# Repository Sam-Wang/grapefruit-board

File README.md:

uMeshFw Grapefruit board / debug platform
==============================================

During the last two years of sparse uMeshFw development I noticed that often a problem or a feature
cannot be properly simulated and tested. Most of the development was done on a qNode4 platform,
which (among the others) lacks support for many required peripherals and is not very debug-friendly.
It was (and still is) meant to be used in "production".

Therefore I decided to specify a new debug board / platform which should ease the development
of the uMeshFw firmware and uMesh protocol stack features.

Also, I had a feeling that qNodeX names are a bit boring.

This repository is a Work in Progress and is still incomplete. Full project description can be
found on the [project page](http://qyx.krtko.org/projects/umeshfw-grapefruit-board/)

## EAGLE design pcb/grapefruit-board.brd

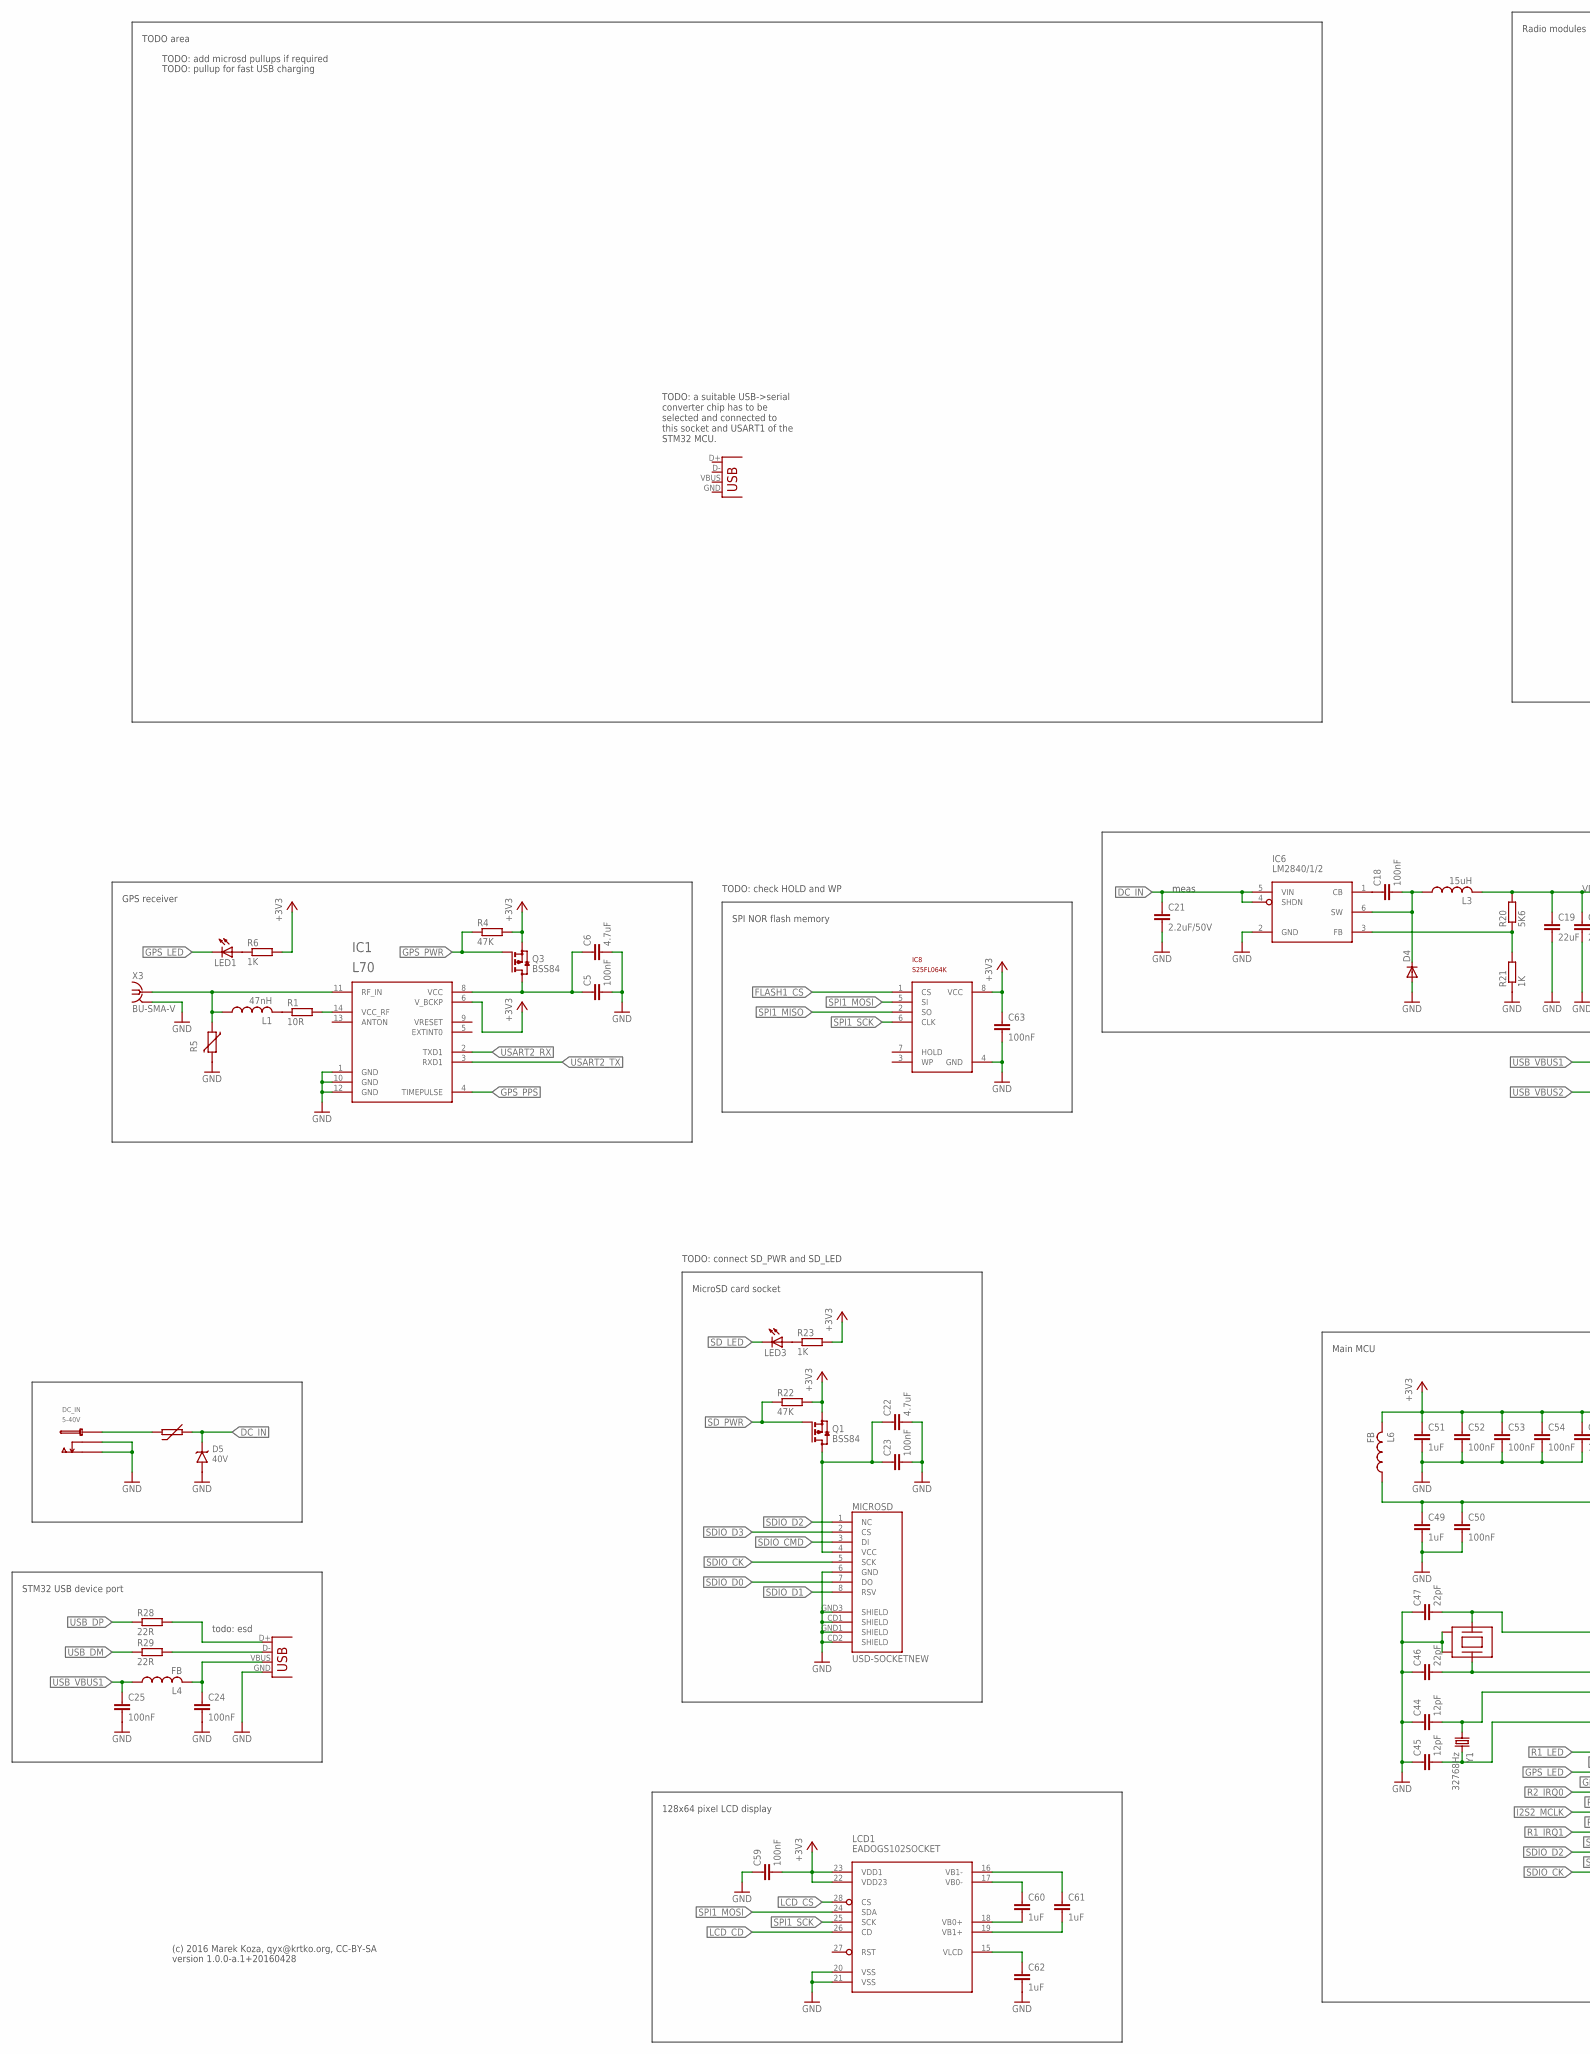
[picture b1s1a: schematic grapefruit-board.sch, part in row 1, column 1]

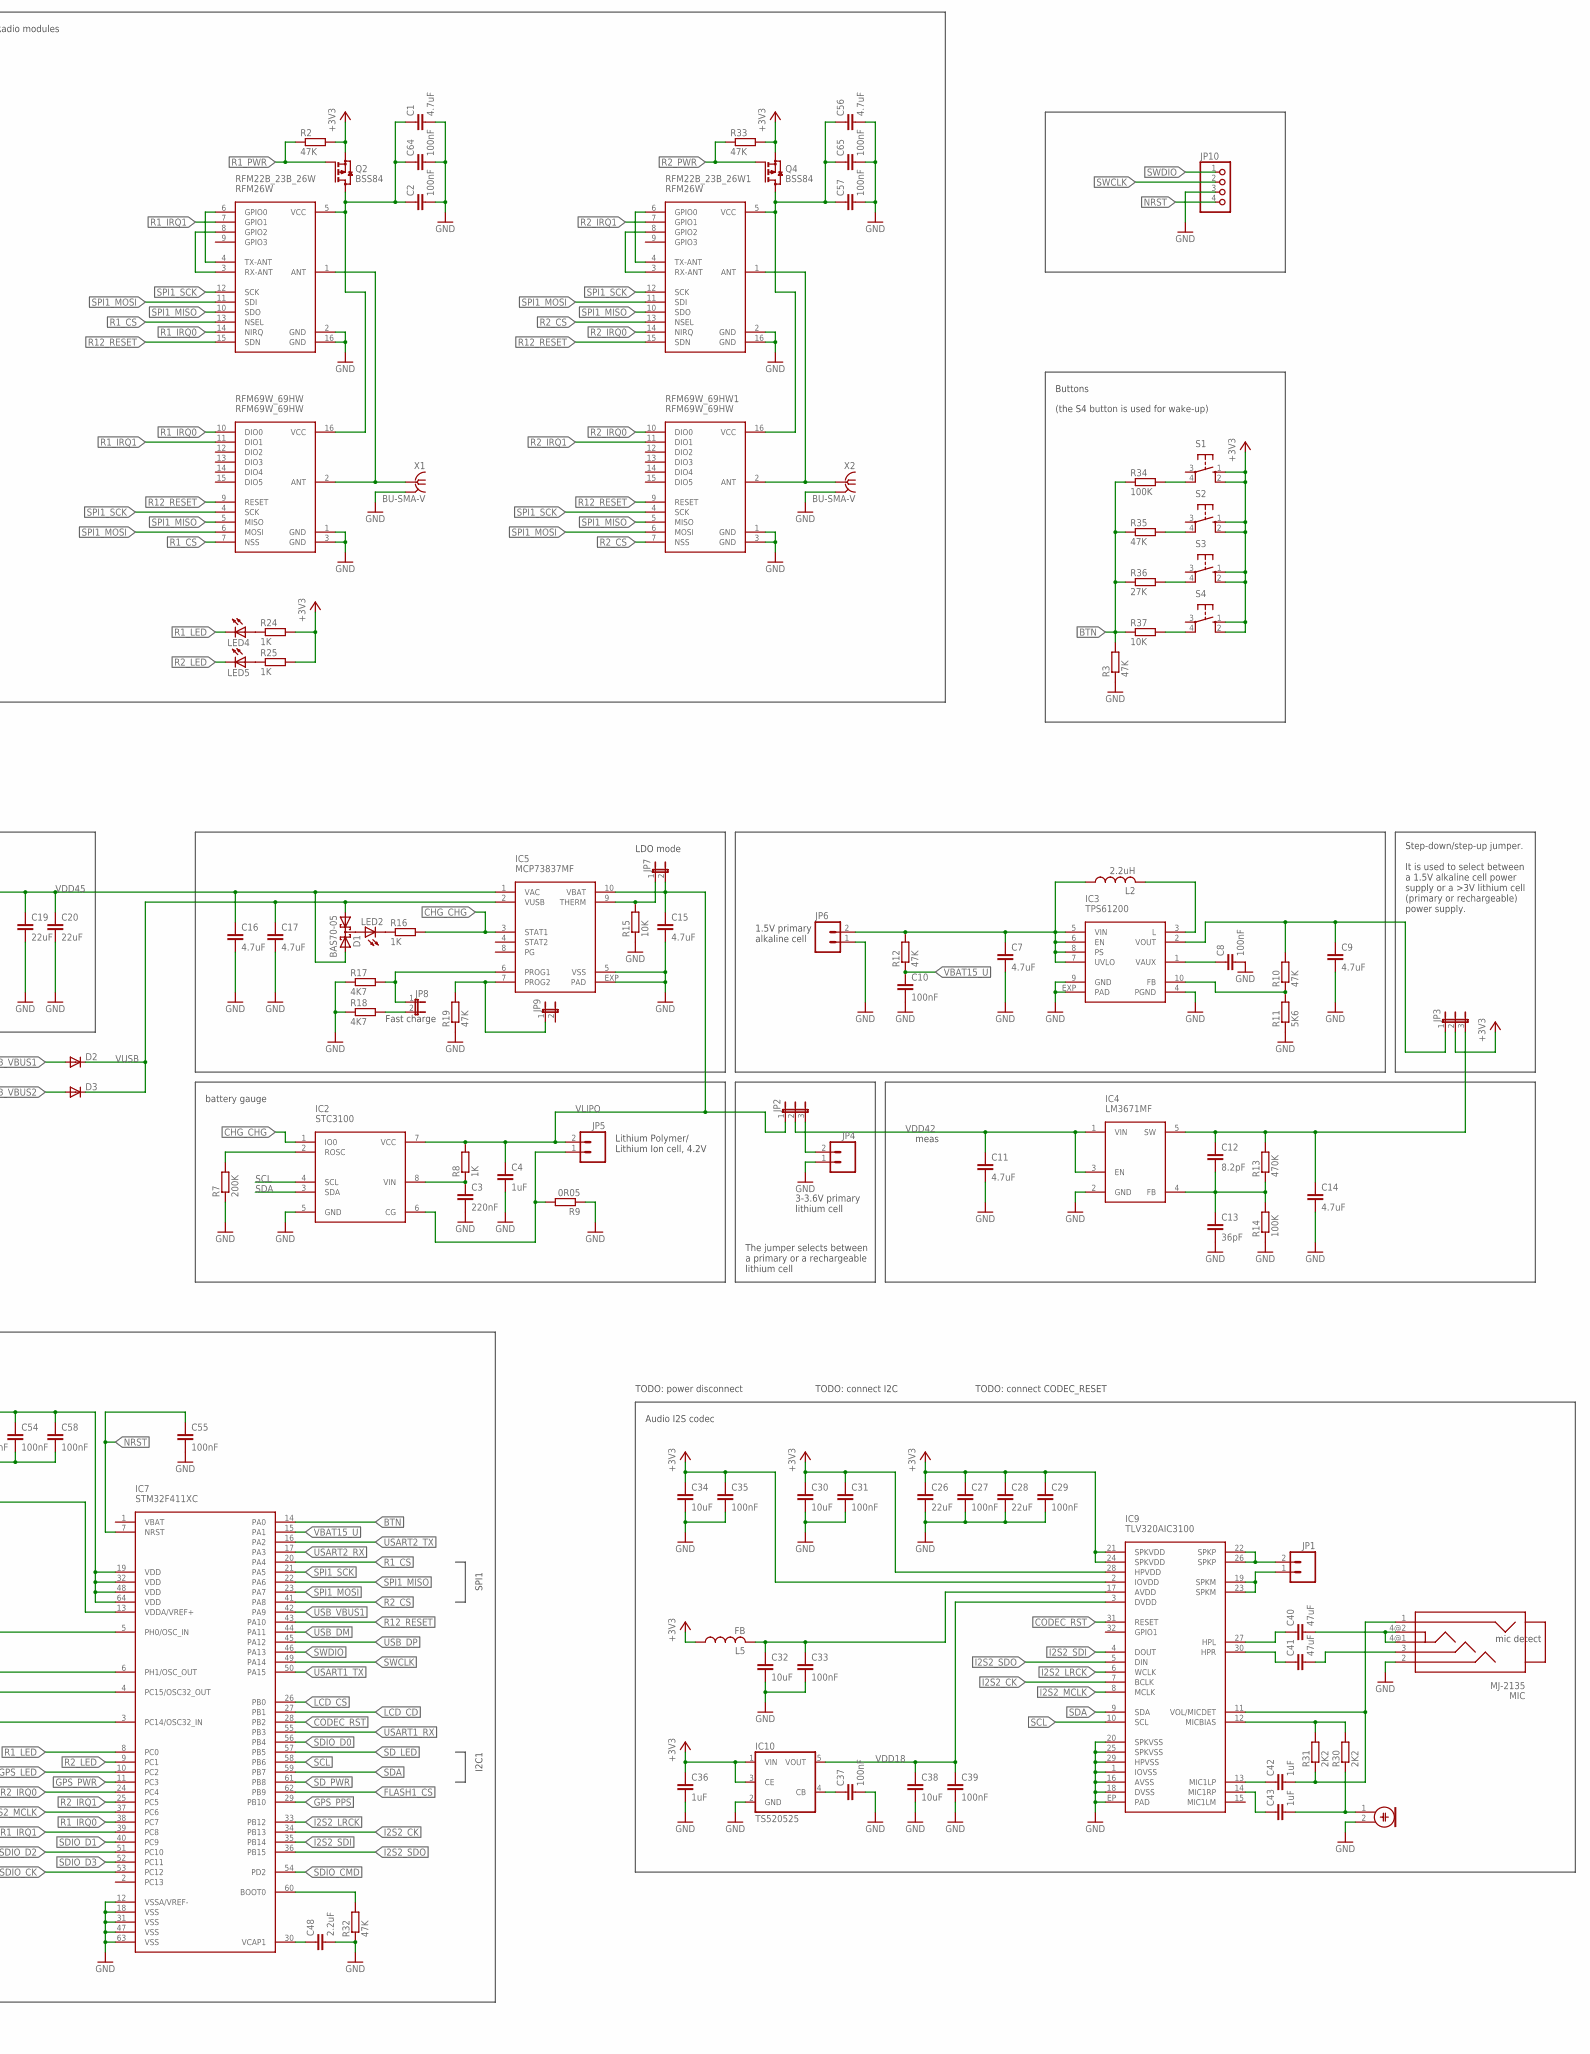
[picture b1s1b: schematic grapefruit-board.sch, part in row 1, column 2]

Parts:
C1, C6, C7, C9, C11, C14, C15, C16, C17, C22, C56: 4.7uF; C0805
C2, C5, C8, C10, C18, C23, C24, C25, C27, C29, C31, C33, C35, C37, C39, C50, C52, C53, C54, C55, C57, C58, C59, C63, C64, C65: 100nF; C0603
C3: 220nF; C0603
C4, C42, C43, C49, C51, C60, C61, C62: 1uF; C0603
C12: 8.2pF; C0603
C13: 36pF; C0603
C19, C20, C26, C28: 22uF; C1206
C21: 2.2uF/50V; C1206
C30, C32, C34, C38: 10uF; C1206
C36: 1uF; C0805
C40, C41: 47uF; C1206
C44, C45: 12pF; C0603
C46, C47: 22pF; C0603
C48: 2.2uF; C0805
D1: BAS70-05; SOT23
D2, D3, D4: DIODE-MICROMELF-W; MICROMELF-W
D5: 40V; SMA_DIODE
DC_IN: 5-40V; DC_JACK
IC1: L70
IC2: STC3100; MSOP8
IC3: TPS61200; DFN10-3X3
IC4: LM3671MF; SOT23-5
IC5: MCP73837MF; DFN10-3X3
IC6: LM2840/1/2; SOT23-6
IC7: STM32F411XC; LQFP64
IC8: S25FL064K; SO-08M
IC9: TLV320AIC3100; QFN32
IC10: TS520525; SOT25
JP1, JP4, JP5, JP6: M02JST-PTH-2; JST-2-PTH
JP2, JP3: JP2E; JP2
JP7, JP8, JP9: JP1E; JP1
JP10: PINHD-1X4; 1X04
L1: 47nH; L2012C
L2: 2.2uH; L2012C
L3: 15uH; L3225M
L4, L5, L6: FB; L2012C
LCD1: EADOGS102SOCKET; EADOGS-SOCKET
LED1, LED2, LED3, LED4, LED5: LEDCHIP-LED0603; CHIP-LED0603
M1: ELECTRET_MICROPHON-WM-62PC/62PK; WM-62PC/62PK
MIC: MJ-2135; JACK_35_4POLE
MICROSD: USD-SOCKETNEW; MICRO-SD-SOCKET-PP
Q1, Q2, Q3, Q4: BSS84; SOT23
R1: 10R; R0603
R2, R3, R4, R10, R12, R19, R22, R32, R33, R35: 47K; R0603
R5: VARISTORCN0805; CT/CN0805
R6, R8, R16, R21, R23, R24, R25: 1K; R0603
R7: 200K; R0603
R9: 0R05; R0805
R11, R20: 5K6; R0603
R13: 470K; R0603
R14, R34: 100K; R0603
R15, R37: 10K; R0603
R17, R18: 4K7; R0603
R28, R29: 22R; R0603
R30, R31: 2K2; R0603
R36: 27K; R0603
RFM22B_23B_26W, RFM22B_23B_26W1: RFM26W; MODULE_16X16_16PIN
RFM69W_69HW, RFM69W_69HW1: RFM69W_69HW; MODULE_20X12_16PIN
S1, S2, S3, S4: 10-XX; B3F-10XX
U$1: XTAL-7M; XTAL_7M
U$2: PTC_FUSE1210; PTC1210
X1, X2, X3: BU-SMA-V
X4, X5: USB-MICROB
Y1: 32768Hz; TC26H

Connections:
+3V3: C26.1, C27.1, C28.1, C29.1, C30.1, C31.1, C34.1, C35.1, C36.1, C51.1, C52.1, C53.1, C54.1, C58.1, C59.2, C63.1, IC1.6 (V_BCKP), IC7.19 (VDD), IC7.32 (VDD), IC7.48 (VDD), IC7.64 (VDD), IC8.8 (VCC), IC9.2 (IOVDD), IC9.21 (SPKVDD), IC9.24 (SPKVDD), IC9.28 (HPVDD), IC10.1 (VIN), IC10.3 (CE), JP3.2, L5.1, L6.2, LCD1.22 (VDD23), LCD1.23 (VDD1), Q1.2 (S), Q2.2 (S), Q3.2 (S), Q4.2 (S), R2.2, R4.2, R6.2, R22.2, R23.2, R24.2, R25.2, R33.2, S1.1 (S), S1.2 (S1), S2.1 (S), S2.2 (S1), S3.1 (S), S3.2 (S1), S4.1 (S), S4.2 (S1)
BTN: IC7.14 (PA0), R3.2, R34.1, R35.1, R36.1, R37.1
BTN1: R34.2, S1.4 (P1)
BTN2: R35.2, S2.4 (P1)
BTN3: R36.2, S3.4 (P1)
BTN4: R37.2, S4.4 (P1)
CHG_CHG: IC2.1 (IO0), IC5.3 (STAT1), R16.2
CODEC_RST: IC7.28 (PB2), IC9.31 (RESET)
DC_IN: C21.1, D5.K, IC6.4 (SHDN), IC6.5 (VIN), U$2.2
FLASH1_CS: IC7.62 (PB9), IC8.1 (CS)
GND: C1.2, C2.2, C3.2, C4.2, C5.2, C6.2, C7.2, C8.2, C9.2, C10.2, C11.2, C13.2, C14.2, C15.2, C16.2, C17.2, C19.2, C20.2, C21.2, C22.2, C23.2, C24.2, C25.2, C26.2, C27.2, C28.2, C29.2, C30.2, C31.2, C32.2, C33.2, C34.2, C35.2, C36.2, C37.2, C38.2, C39.2, C44.1, C45.1, C46.1, C47.1, C48.2, C49.2, C50.2, C51.2, C52.2, C53.2, C54.2, C55.2, C56.2, C57.2, C58.2, C59.1, C62.2, C63.2, C64.2, C65.2, D4.A, D5.A, DC_IN.O, DC_IN.OSW, IC1.1 (GND), IC1.10 (GND), IC1.12 (GND), IC2.5 (GND), IC3.4 (PGND), IC3.9 (GND), IC3.EXP (PAD), IC4.2 (GND), IC5.5 (VSS), IC5.EXP (PAD), IC6.2 (GND), IC7.12 (VSSA/VREF-), IC7.18 (VSS), IC7.31 (VSS), IC7.47 (VSS), IC7.63 (VSS), IC8.4 (GND), IC9.1 (IOVSS), IC9.16 (AVSS), IC9.18 (DVSS), IC9.20 (SPKVSS), IC9.25 (SPKVSS), IC9.29 (HPVSS), IC9.EP (PAD), IC10.2 (GND), JP4.1, JP6.1, JP10.3, LCD1.20 (VSS), LCD1.21 (VSS), M1.2, MIC.2, MICROSD.6 (GND), MICROSD.CD1 (SHIELD), MICROSD.CD2 (SHIELD), MICROSD.GND1 (SHIELD), MICROSD.GND3 (SHIELD), R3.1, R5.2, R7.1, R9.1, R11.1, R14.1, R15.1, R17.1, R18.1, R19.1, R21.1, R32.1, RFM22B_23B_26W.2 (GND), RFM22B_23B_26W.16 (GND), RFM22B_23B_26W1.2 (GND), RFM22B_23B_26W1.16 (GND), RFM69W_69HW.1 (GND), RFM69W_69HW.3 (GND), RFM69W_69HW1.1 (GND), RFM69W_69HW1.3 (GND), U$1.2 (G1), U$1.4 (G2), X1.2, X1.3 (2), X1.4 (2), X1.5 (2), X2.2, X2.3 (2), X2.4 (2), X2.5 (2), X3.2, X3.3 (2), X3.4 (2), X3.5 (2), X4.GND
GPS_LED: IC7.10 (PC2), LED1.C
GPS_PPS: IC1.4 (TIMEPULSE), IC7.29 (PB10)
GPS_PWR: IC7.11 (PC3), Q3.1 (G), R4.1
I2S2_CK: IC7.34 (PB13), IC9.7 (BCLK)
I2S2_LRCK: IC7.33 (PB12), IC9.6 (WCLK)
I2S2_MCLK: IC7.37 (PC6), IC9.8 (MCLK)
I2S2_SDI: IC7.35 (PB14), IC9.4 (DOUT)
I2S2_SDO: IC7.36 (PB15), IC9.5 (DIN)
LCD_CD: IC7.27 (PB1), LCD1.26 (CD)
LCD_CS: IC7.26 (PB0), LCD1.28 (CS)
unnamed: RFM22B_23B_26W1.1 (ANT), RFM69W_69HW1.2 (ANT), X2.1
unnamed: RFM22B_23B_26W.1 (ANT), RFM69W_69HW.2 (ANT), X1.1
unnamed: L1.2, R1.1
unnamed: IC1.11 (RF_IN), L1.1, R5.1, X3.1
unnamed: IC1.14 (VCC_RF), R1.2
unnamed: C1.1, C2.1, C64.1, Q2.3 (D), RFM22B_23B_26W.5 (VCC), RFM69W_69HW.16 (VCC)
unnamed: LED1.A, R6.1
unnamed: C5.1, C6.1, IC1.8 (VCC), Q3.3 (D)
unnamed: C7.1, IC3.5 (VIN), IC3.6 (EN), IC3.7 (UVLO), IC3.8 (PS), JP6.2, L2.1, R12.2
unnamed: JP2.3, JP4.2
unnamed: IC2.6 (CG), JP5.1, R9.2
unnamed: IC5.9 (THERM), JP7.1, R15.2
unnamed: IC5.6 (PROG1), JP8.1, R17.2
unnamed: C12.1, C14.1, IC4.5 (SW), JP3.3, R13.2
unnamed: C3.1, IC2.8 (VIN), R8.1
unnamed: C8.1, IC3.1 (VAUX)
unnamed: IC2.2 (ROSC), R7.2
unnamed: C9.1, IC3.2 (VOUT), JP3.1, R10.2
unnamed: IC3.3 (L), L2.2
unnamed: C12.2, C13.1, IC4.4 (FB), R13.1, R14.2
unnamed: IC3.10 (FB), R10.1, R11.2
unnamed: JP8.2, R18.2
unnamed: LED2.C, R16.1
unnamed: D1.3 (C), LED2.A
unnamed: IC5.7 (PROG2), JP9.1, R19.2
unnamed: C18.1, IC6.1 (CB)
unnamed: C18.2, D4.C, IC6.6 (SW), L3.1
unnamed: IC6.3 (FB), R20.1, R21.2
unnamed: C22.1, C23.1, MICROSD.4 (VCC), Q1.3 (D)
unnamed: LED3.A, R23.1
unnamed: LED4.A, R24.1
unnamed: LED5.A, R25.1
unnamed: R28.2, X4.D+
unnamed: R29.2, X4.D-
unnamed: C24.1, L4.2, X4.VBUS
unnamed: C43.1, IC9.14 (MIC1RP)
unnamed: C32.1, C33.1, IC9.17 (AVDD), L5.2
unnamed: C37.1, IC10.4 (CB)
unnamed: C40.2, MIC.4@1 (4), MIC.4@2 (4)
unnamed: C41.2, MIC.3
unnamed: C41.1, IC9.30 (HPR)
unnamed: C40.1, IC9.27 (HPL)
unnamed: C44.2, IC7.4 (PC15/OSC32_OUT), Y1.1
unnamed: C42.1, IC9.13 (MIC1LP)
unnamed: C42.2, IC9.11 (VOL/MICDET), MIC.1, R31.1
unnamed: C43.2, M1.1, R30.1
unnamed: IC9.12 (MICBIAS), R30.2, R31.2
unnamed: IC9.22 (SPKP), IC9.26 (SPKP), JP1.2
unnamed: IC9.19 (SPKM), IC9.23 (SPKM), JP1.1
unnamed: C45.2, IC7.3 (PC14/OSC32_IN), Y1.2
unnamed: DC_IN.C, U$2.1
unnamed: C47.2, IC7.5 (PH0/OSC_IN), U$1.1
unnamed: C46.2, IC7.6 (PH1/OSC_OUT), U$1.3 (2)
unnamed: C56.1, C57.1, C65.1, Q4.3 (D), RFM22B_23B_26W1.5 (VCC), RFM69W_69HW1.16 (VCC)
unnamed: IC7.60 (BOOT0), R32.2
unnamed: C48.1, IC7.30 (VCAP1)
unnamed: C49.1, C50.1, IC7.13 (VDDA/VREF+), L6.1
unnamed: C60.1, LCD1.17 (VB0-)
unnamed: C61.1, LCD1.16 (VB1-)
unnamed: C60.2, LCD1.18 (VB0+)
unnamed: C61.2, LCD1.19 (VB1+)
unnamed: C62.1, LCD1.15 (VLCD)
NRST: C55.1, IC7.7 (NRST), JP10.4
R1_CS: IC7.20 (PA4), RFM22B_23B_26W.13 (NSEL), RFM69W_69HW.7 (NSS)
R1_DIO0: RFM22B_23B_26W.4 (TX-ANT), RFM22B_23B_26W.6 (GPIO0)
R1_DIO2: RFM22B_23B_26W.3 (RX-ANT), RFM22B_23B_26W.8 (GPIO2)
R1_IRQ0: IC7.38 (PC7), RFM22B_23B_26W.14 (NIRQ), RFM69W_69HW.10 (DIO0)
R1_IRQ1: IC7.39 (PC8), RFM22B_23B_26W.7 (GPIO1), RFM69W_69HW.11 (DIO1)
R1_LED: IC7.8 (PC0), LED4.C
R1_PWR: Q2.1 (G), R2.1
R2_CS: IC7.41 (PA8), RFM22B_23B_26W1.13 (NSEL), RFM69W_69HW1.7 (NSS)
R2_DIO0: RFM22B_23B_26W1.4 (TX-ANT), RFM22B_23B_26W1.6 (GPIO0)
R2_DIO2: RFM22B_23B_26W1.3 (RX-ANT), RFM22B_23B_26W1.8 (GPIO2)
R2_IRQ0: IC7.24 (PC4), RFM22B_23B_26W1.14 (NIRQ), RFM69W_69HW1.10 (DIO0)
R2_IRQ1: IC7.25 (PC5), RFM22B_23B_26W1.7 (GPIO1), RFM69W_69HW1.11 (DIO1)
R2_LED: IC7.9 (PC1), LED5.C
R2_PWR: Q4.1 (G), R33.1
R12_RESET: IC7.43 (PA10), RFM22B_23B_26W.15 (SDN), RFM22B_23B_26W1.15 (SDN), RFM69W_69HW.9 (RESET), RFM69W_69HW1.9 (RESET)
SCL: IC2.4 (SCL), IC7.58 (PB6), IC9.10 (SCL)
SDA: IC2.3 (SDA), IC7.59 (PB7), IC9.9 (SDA)
SDIO_CK: IC7.53 (PC12), MICROSD.5 (SCK)
SDIO_CMD: IC7.54 (PD2), MICROSD.3 (DI)
SDIO_D0: IC7.56 (PB4), MICROSD.7 (DO)
SDIO_D1: IC7.40 (PC9), MICROSD.8 (RSV)
SDIO_D2: IC7.51 (PC10), MICROSD.1 (NC)
SDIO_D3: IC7.52 (PC11), MICROSD.2 (CS)
SD_LED: IC7.57 (PB5), LED3.C
SD_PWR: IC7.61 (PB8), Q1.1 (G), R22.1
SPI1_MISO: IC7.22 (PA6), IC8.2 (SO), RFM22B_23B_26W.10 (SDO), RFM22B_23B_26W1.10 (SDO), RFM69W_69HW.5 (MISO), RFM69W_69HW1.5 (MISO)
SPI1_MOSI: IC7.23 (PA7), IC8.5 (SI), LCD1.24 (SDA), RFM22B_23B_26W.11 (SDI), RFM22B_23B_26W1.11 (SDI), RFM69W_69HW.6 (MOSI), RFM69W_69HW1.6 (MOSI)
SPI1_SCK: IC7.21 (PA5), IC8.6 (CLK), LCD1.25 (SCK), RFM22B_23B_26W.12 (SCK), RFM22B_23B_26W1.12 (SCK), RFM69W_69HW.4 (SCK), RFM69W_69HW1.4 (SCK)
SWCLK: IC7.49 (PA14), JP10.2
SWDIO: IC7.46 (PA13), JP10.1
USART1_RX: IC7.55 (PB3)
USART1_TX: IC7.50 (PA15)
USART2_RX: IC1.2 (TXD1), IC7.17 (PA3)
USART2_TX: IC1.3 (RXD1), IC7.16 (PA2)
USB_DM: IC7.44 (PA11), R29.1
USB_DP: IC7.45 (PA12), R28.1
USB_VBUS1: C25.1, D2.A, IC7.42 (PA9), L4.1
USB_VBUS2: D3.A
VBAT15_U: C10.1, IC7.15 (PA1), R12.1
VDD18: C38.1, C39.1, IC9.3 (DVDD), IC10.5 (VOUT)
VDD42: C11.1, IC4.1 (VIN), IC4.3 (EN), JP2.2
VDD45: C16.1, C19.1, C20.1, D1.2 (A2), IC5.1 (VAC), L3.2, R20.2
VLIPO: C4.1, C15.1, IC2.7 (VCC), IC5.10 (VBAT), JP2.1, JP5.2, JP7.2, R8.2
VUSB: C17.1, D1.1 (A1), D2.C, D3.C, IC5.2 (VUSB)

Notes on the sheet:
mic detect
battery gauge
Lithium Polymer/ Lithium Ion cell, 4.2V
3-3.6V primary lithium cell
1.5V primary alkaline cell
meas
Step-down/step-up jumper. It is used to select between a 1.5V alkaline cell power supply or a >3V lithium cell (primary or rechargeable) power supply.
The jumper selects between a primary or a rechargeable lithium cell
TODO: pullup for fast USB charging
LDO mode
Fast charge
todo: esd
Buttons
TODO area
TODO: a suitable USB->serial converter chip has to be selected and connected to this socket and USART1 of the STM32 MCU.
STM32 USB device port
MicroSD card socket
TODO: add microsd pullups if required
Main MCU
Audio I2S codec
Radio modules
(c) 2016 Marek Koza, qyx@krtko.org, CC-BY-SA
version 1.0.0-a.1+20160428
GPS receiver
TODO: connect SD_PWR and SD_LED
TODO: power disconnect
TODO: connect I2C
TODO: connect CODEC_RESET
SPI1
I2C1
TODO: check HOLD and WP
SPI NOR flash memory
128x64 pixel LCD display
(the S4 button is used for wake-up)

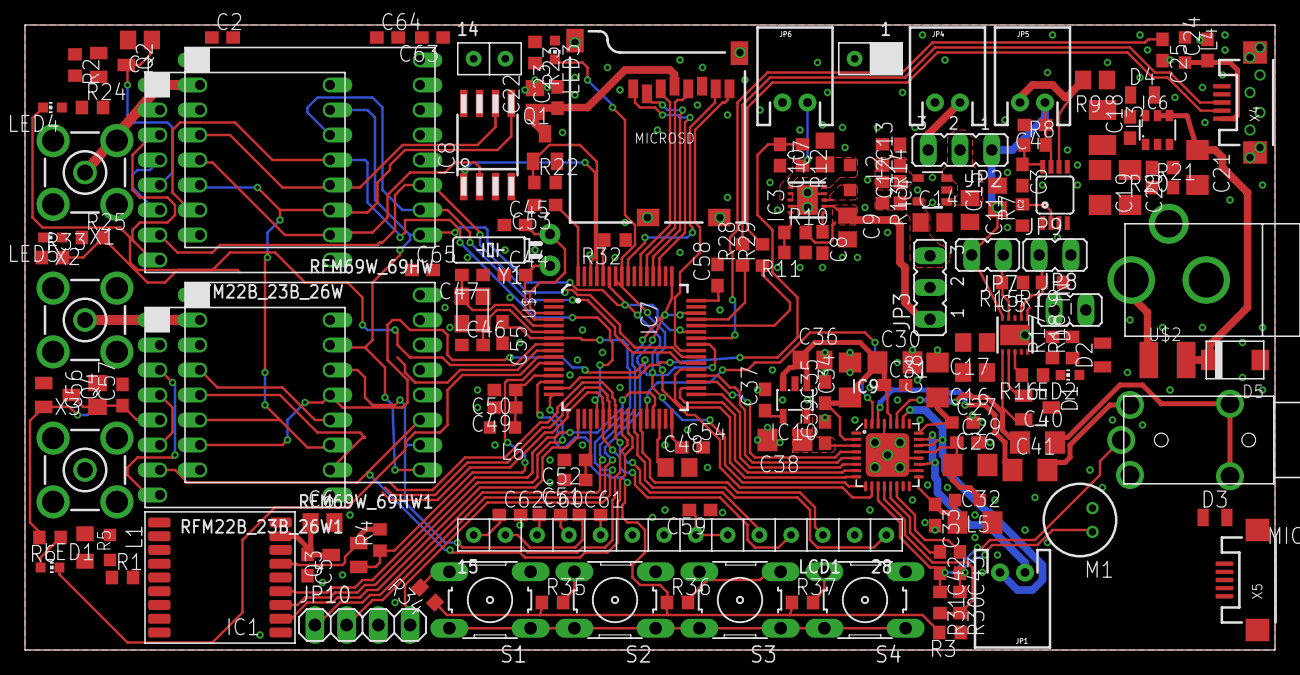
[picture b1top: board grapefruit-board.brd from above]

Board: 2 copper layers, 100.0 x 50.0 mm, 161 parts (0 on the bottom side), 125 nets.

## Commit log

2016-02-17 iAdd Eagle gitignore file
2016-02-17 Add basic schematic and layout
2016-02-17 Add a grapefruit picture from the Wikipedia
2016-02-17 Add README.md file
2016-04-28 Change values of some components, add SWD pin header
2016-04-28 Add DC IN input
2016-04-29 Resolve the remaining unconnected parts

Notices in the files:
parts and their libraries:
SparkFun: Licensing: CC v3.0 Share-Alike You are welcome to use this library for commercial purposes.
